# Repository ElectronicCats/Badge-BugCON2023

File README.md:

# Badge BugCON 2023

Badge de la resistencia BugCON 2023 #unetealaresistencia

## Características

- ESP32S3 o RP2040
- UART
- Bluetooth (ESP32S3)
- WiFi (ESP32S3)
- Baterias AA

## License

Diseñado por Electronic Cats para BugCON 2023

Electronic Cats invests time and resources in providing this open-source design. Please support Electronic Cats and open-source hardware by purchasing products from Electronic Cats!

Hardware released under an CERN Open Hardware Licence v1.2. See the LICENSE_HARDWARE file for more information.

Electronic Cats and BugCON is a registered trademark. Please do not use if you sell these PCBs.

Sept 2023

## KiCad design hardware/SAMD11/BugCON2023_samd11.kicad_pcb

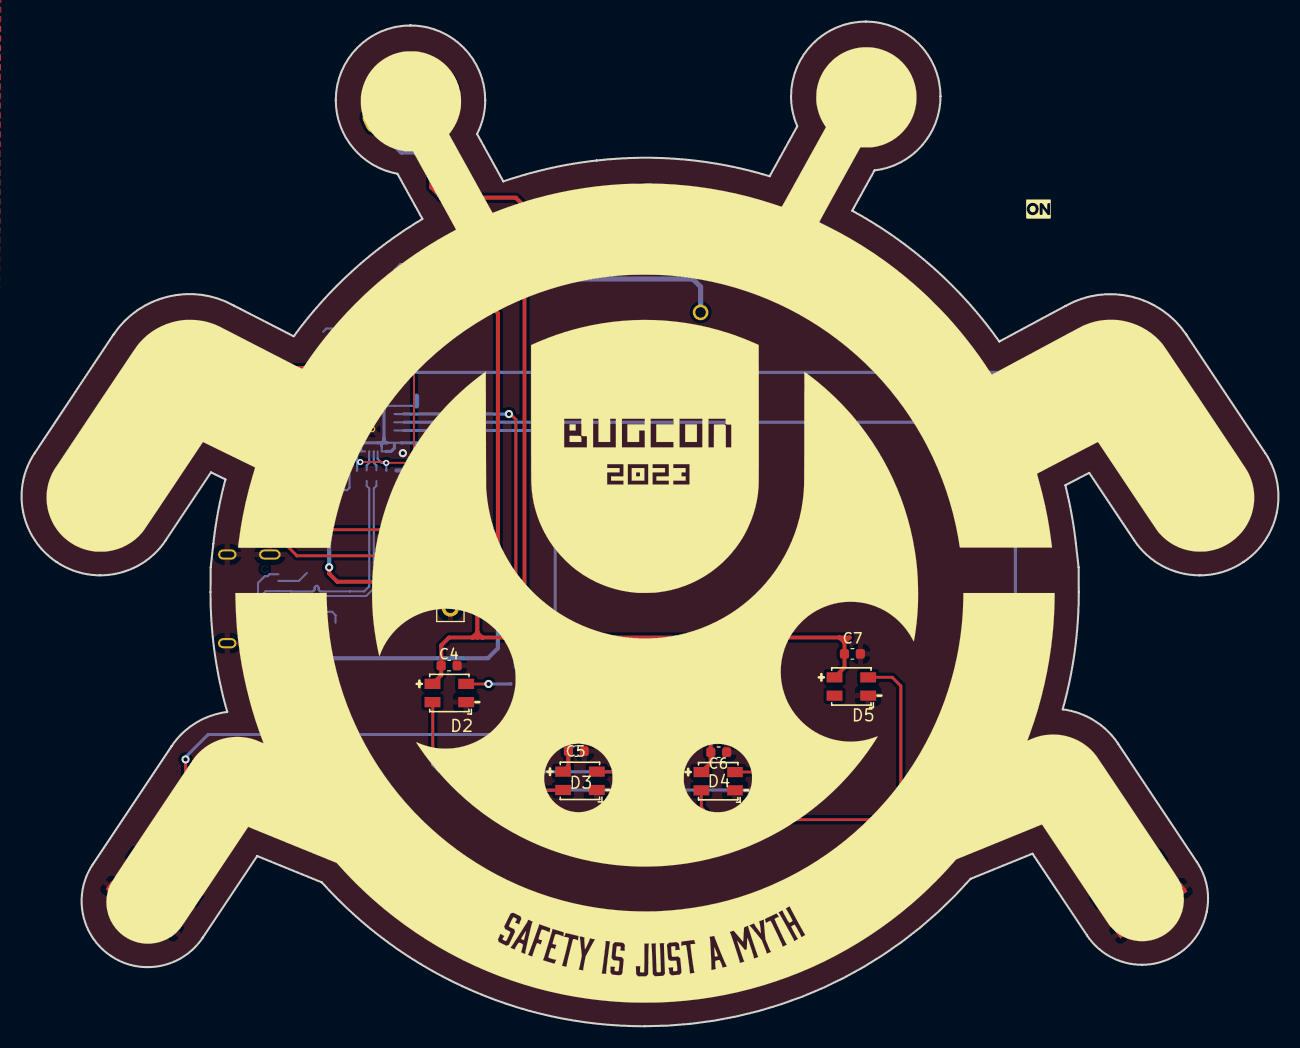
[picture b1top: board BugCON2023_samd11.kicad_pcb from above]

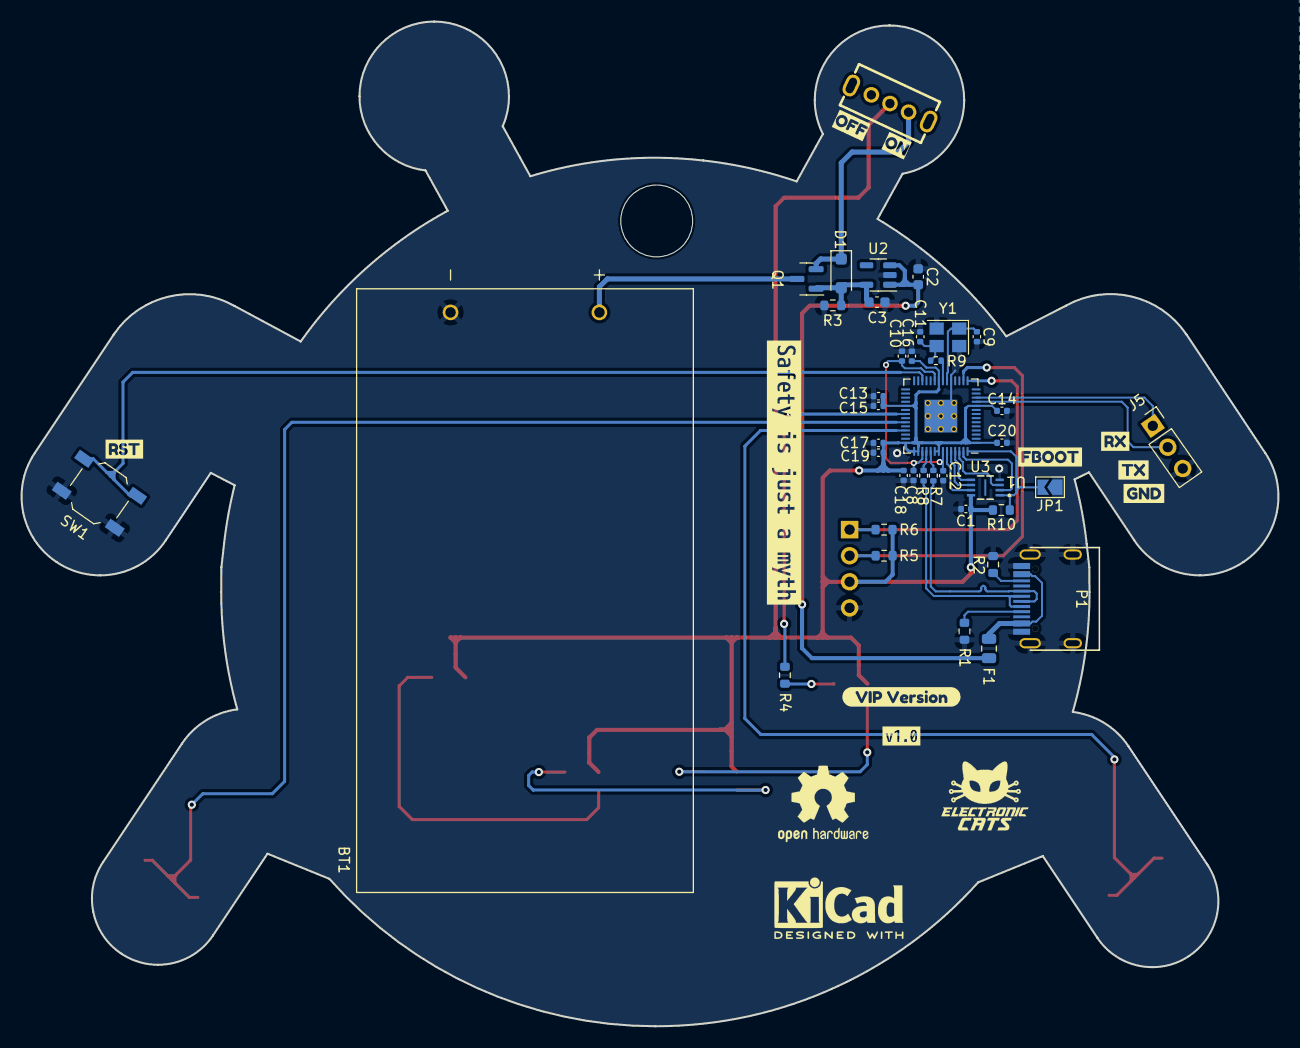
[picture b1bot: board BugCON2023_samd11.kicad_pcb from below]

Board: 2 copper layers, 122.4 x 97.9 mm, 63 parts (49 on the bottom side), 35 nets.

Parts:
BT1: Battery_Cell; BAT_2462
C1, C10, C12, C14, C15, C16, C17, C18, C19, C20: 0.1uF; C_0402_1005Metric
C2, C3: 10uF; C_0603_1608Metric
C4, C5, C6, C7: 0.1uF; C_0603_1608Metric
C8, C13: 1uF; C_0402_1005Metric
C9, C11: 27pF; C_0402_1005Metric
D1: MBR120; D_SOD-123F
D2, D3, D4, D5: WS2812B; LED-SMD_4P-L3.5-W3.5-TL_WS2812B
F1: 0.5A; Fuse_0805_2012Metric
J1: I2C; PinSocket_1x04_P2.54mm_Vertical
J5: Serial; PinSocket_1x03_P2.54mm_Vertical
JP1: BOOT; SolderJumper-2_P1.3mm_Open_TrianglePad1.0x1.5mm
P1: USB_C_Plug_USB2.0; C393939
Q1: DMG3415U-7; SOT-23
R1, R2: 5k1; R_0603_1608Metric
R3: 100K; R_0603_1608Metric
R4: 470; R_0603_1608Metric
R5, R6: 4.7; R_0603_1608Metric
R7, R8: 27; R_0402_1005Metric
R9: 1k; R_0402_1005Metric
R10: 10K; R_0603_1608Metric
Ref**: Val**; Bugcon_svg
SW1: RESET; SW_SPST_TL3342
SW2: ON; SW-TH_SK12D07VG4
SW3, SW4: SW_Push; SW_SPST_TL3342
U1: W25Q16JV; W25Q16JVUXIQ_WIN
U2: AP2112K-3.3; SOT-23-5
U3: RP2040; QFN-56-1EP_7x7mm_P0.4mm_EP3.2x3.2mm
Y1: 12MHz; Crystal_SMD_3225-4Pin_3.2x2.5mm
kibuzzard-652DCDAF: G***; kibuzzard-652DCDAF
kibuzzard-652DCDD3: G***; kibuzzard-652DCDD3
kibuzzard-652DCDF1: G***; kibuzzard-652DCDF1
kibuzzard-652EA30A: G***; kibuzzard-652EA30A
kibuzzard-652EA51A, kibuzzard-652EA51A#2: G***; kibuzzard-652EA51A
kibuzzard-6536E42E: G***; kibuzzard-6536E42E
kibuzzard-6536E385: G***; kibuzzard-6536E385
kibuzzard-6536E415: G***; kibuzzard-6536E415
kibuzzard-6536E422: G***; kibuzzard-6536E422
kibuzzard-6536E471: G***; kibuzzard-6536E471
kibuzzard-6537FB4E: G***; kibuzzard-6537FB4E

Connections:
+1V2: C8.1, C10.1, C12.1, U3.23 (DVDD), U3.45 (VREG_VOUT), U3.50 (DVDD)
+3.3V: C1.1, C4.2, C5.2, C6.2, C7.2, C13.1, C14.1, C15.1, C16.1, C17.1, C18.1, C19.1, C20.1, D2.1 (VDD), D3.1 (VDD), D4.1 (VDD), D5.1 (VDD), J1.3, R5.2, R6.1, R10.1, SW2.2 (B), U1.8 (VCC), U3.1 (IOVDD), U3.10 (IOVDD), U3.22 (IOVDD), U3.33 (IOVDD), U3.42 (IOVDD), U3.43 (ADC_AVDD), U3.44 (VREG_IN), U3.48 (USB_VDD), U3.49 (IOVDD)
+3V3: C3.1, D1.2 (A), Q1.1 (G), R3.1, U2.5 (VOUT)
+BATT: BT1.1 (+), Q1.3 (D)
/D+: P1.A6 (D+), R7.1
/D-: P1.A7 (D-), R8.1
/PB1: SW3.1, U3.39 (GPIO27_ADC1)
/PB2: SW4.1, U3.37 (GPIO25)
/PIN: R4.1, U3.35 (GPIO23)
/QSPI_SCK: U1.6 (CLK), U3.52 (QSPI_SCLK)
/QSPI_SD0: U1.5 (DI(IO0)), U3.53 (QSPI_SD0)
/QSPI_SD1: U1.2 (DO(IO1)), U3.55 (QSPI_SD1)
/QSPI_SD2: U1.3 (IO2), U3.54 (QSPI_SD2)
/QSPI_SD3: U1.7 (IO3), U3.51 (QSPI_SD3)
/QSPI_SS: JP1.2 (B), R10.2, U1.1 (~CS), U3.56 (QSPI_SS)
/RD+: R7.2, U3.47 (USB_DP+)
/RD-: R8.2, U3.46 (USB_DM-)
/RESET: SW1.1, U3.26 (RUN)
/RX: J5.1, U3.12 (GPIO9)
/SCL: J1.2, R5.1, U3.16 (GPIO13)
/SDA: J1.1, R6.2, U3.15 (GPIO12)
/TX: J5.2, U3.11 (GPIO8)
GND: BT1.2 (-), C1.2, C2.2, C3.2, C4.1, C5.1, C6.1, C7.1, C8.2, C9.2, C10.2, C11.2, C12.2, C13.2, C14.2, C15.2, C16.2, C17.2, C18.2, C19.2, C20.2, D2.3 (VSS), D3.3 (VSS), D4.3 (VSS), D5.3 (VSS), J1.4, J5.3, JP1.1 (A), P1.A1 (GND), P1.S1 (SHIELD), R1.1, R2.1, R3.2, SW1.2, SW3.2, SW4.2, U1.4 (GND), U2.2 (GND), U3.19 (TESTEN), U3.57 (GND), Y1.2, Y1.4
unnamed: C11.1, R9.1, Y1.3
unnamed: D1.1 (K), Q1.2 (S), SW2.1 (A)
unnamed: D2.4 (DIN), R4.2
unnamed: D2.2 (DOUT), D3.4 (DIN)
unnamed: D3.2 (DOUT), D4.4 (DIN)
unnamed: D4.2 (DOUT), D5.4 (DIN)
unnamed: F1.1, P1.A4 (VBUS)
unnamed: P1.A5 (CC), R1.2
unnamed: P1.B5 (VCONN), R2.2
unnamed: C9.1, U3.20 (XIN), Y1.1
unnamed: R9.2, U3.21 (XOUT)
VBUS: C2.1, F1.2, U2.1 (VIN), U2.3 (EN)

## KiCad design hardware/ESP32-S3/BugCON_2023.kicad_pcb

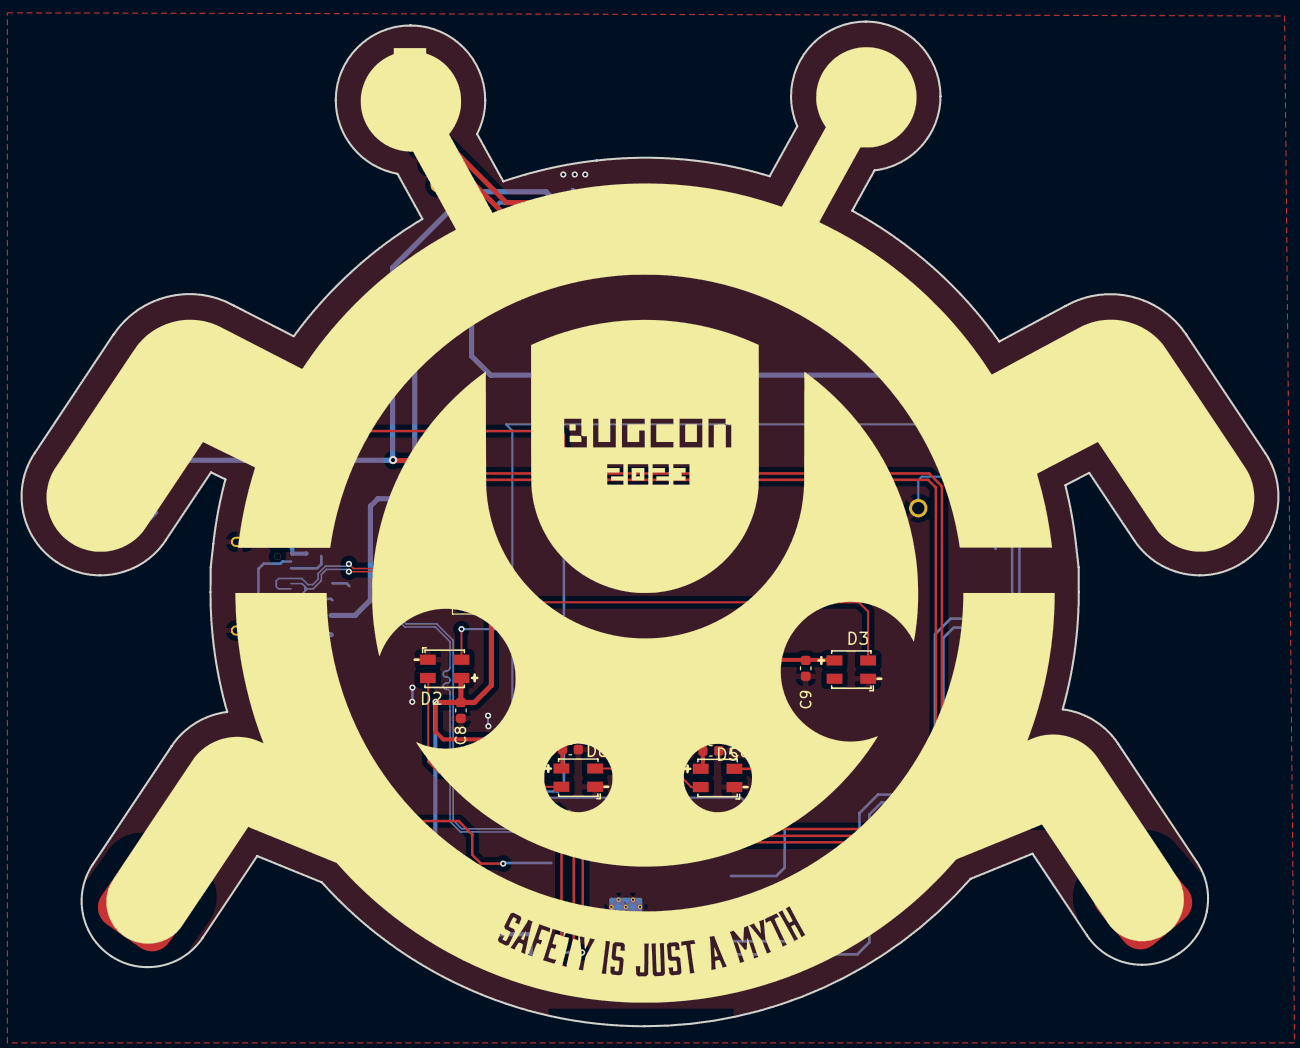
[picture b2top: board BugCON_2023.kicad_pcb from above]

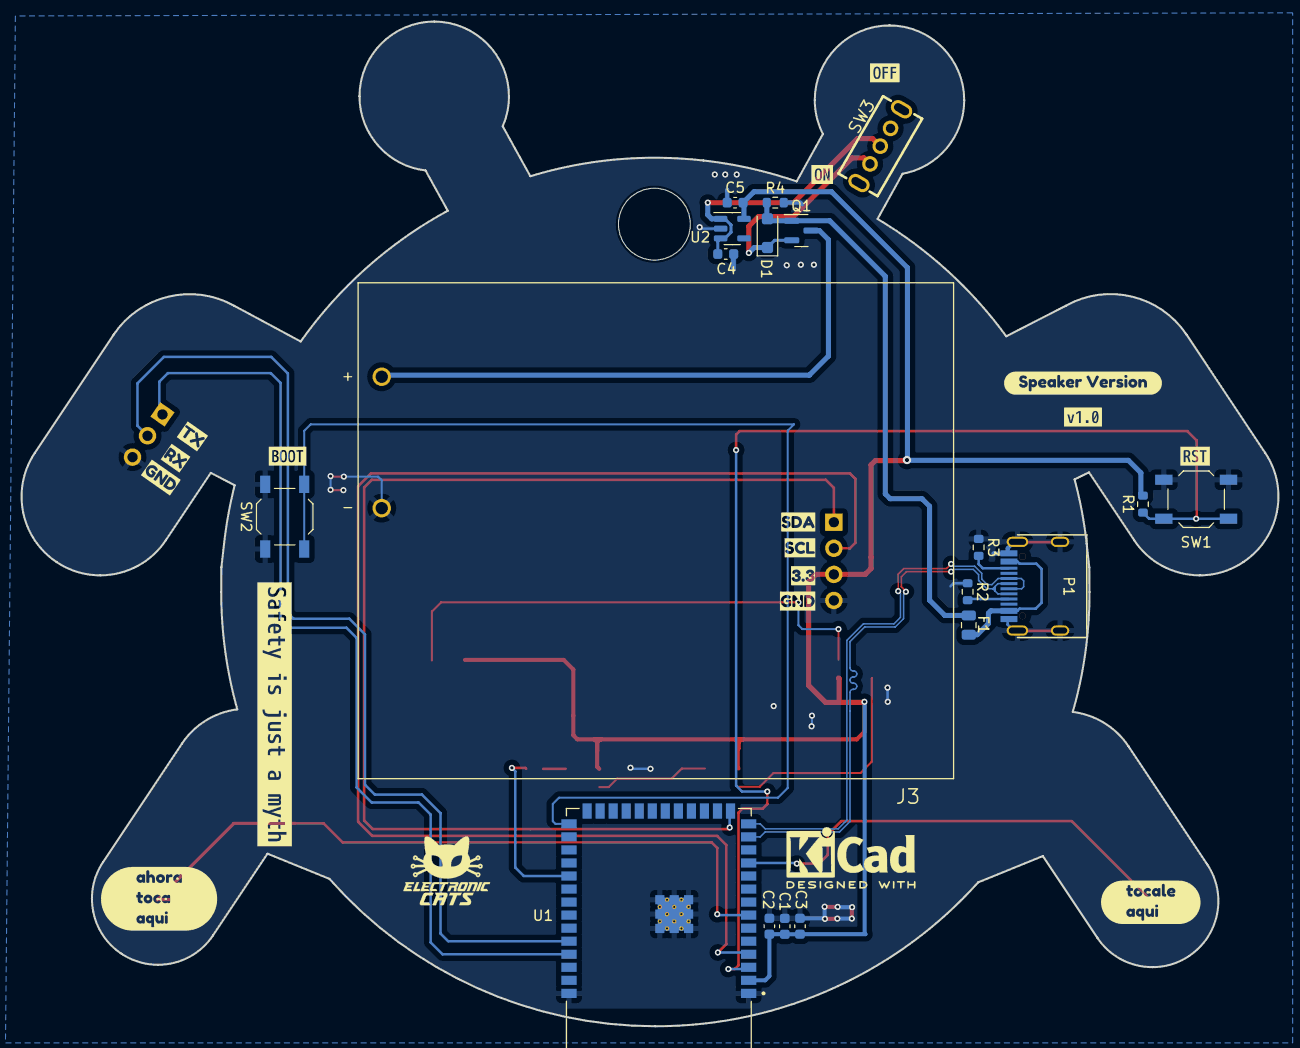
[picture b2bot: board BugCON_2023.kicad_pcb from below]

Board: 2 copper layers, 122.4 x 97.9 mm, 50 parts (35 on the bottom side), 24 nets.

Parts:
C1: 1uF; C_0603_1608Metric
C2, C3, C4, C5: 10uF; C_0603_1608Metric
C6, C7, C8, C9: 0.1uF; C_0603_1608Metric
D1: MBR120; D_SOD-123F
D2, D3, D5, D6: WS2812B; LED-SMD_4P-L3.5-W3.5-TL_WS2812B
F1: 0.5A; Fuse_0805_2012Metric
J1: Conn_01x04_Pin; PinSocket_1x04_P2.54mm_Vertical
J3: Conn_01x02; BAT_12BH331P-GR
J4, J5: Conn_01x01_Pin; PinHeader_1x01_P1.00mm_Horizontal
J6: SERIAL; PinSocket_1x03_P2.54mm_Vertical
P1: USB_C_Plug_USB2.0; C393939
Q1: DMG3415U-7; SOT-23
R1: 10K; R_0603_1608Metric
R2, R3: 5k1; R_0603_1608Metric
R4: 100K; R_0603_1608Metric
R9: 470; R_0603_1608Metric
Ref**: Val**; Bugcon_svg
SW1: RESET; SW_SPST_TL3342
SW2: GPIO; SW_SPST_TL3342
SW3: ON; SW-TH_SK12D07VG4
U1: ESP32-S3-WROOM-1-N4; XCVR_ESP32-S3-WROOM-1-N8R2
U2: AP2112K-3.3; SOT-23-5
kibuzzard-652D8C8F: G***; kibuzzard-652D8C8F
kibuzzard-652D8CA2: G***; kibuzzard-652D8CA2
kibuzzard-652EA3B8: G***; kibuzzard-652EA3B8
kibuzzard-652EA5CF: G***; kibuzzard-652EA5CF
kibuzzard-652EA5F7: G***; kibuzzard-652EA5F7
kibuzzard-652EA30A: G***; kibuzzard-652EA30A
kibuzzard-652EA32D: G***; kibuzzard-652EA32D
kibuzzard-652EA37F: G***; kibuzzard-652EA37F
kibuzzard-652EA51A: G***; kibuzzard-652EA51A
kibuzzard-652EA56E: G***; kibuzzard-652EA56E
kibuzzard-652EA350: G***; kibuzzard-652EA350
kibuzzard-652EA580: G***; kibuzzard-652EA580
kibuzzard-6515D6F9: G***; kibuzzard-6515D6F9
kibuzzard-6515D7CD: G***; kibuzzard-6515D7CD
kibuzzard-6515D70B: G***; kibuzzard-6515D70B
kibuzzard-6515D795, kibuzzard-6515D795#2: G***; kibuzzard-6515D795

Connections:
+3V3: C1.1, C2.1, C3.1, C5.1, C6.2, C7.2, C8.2, C9.2, D2.1 (VDD), D3.1 (VDD), D5.1 (VDD), D6.1 (VDD), J1.3, R1.2, U1.2 (3V3), U2.5 (VOUT)
+BATT: J3.1, Q1.3 (D)
/BOOT: SW2.2, U1.27 (IO0)
/D+: P1.A6 (D+), U1.14 (IO20)
/D-: P1.A7 (D-), U1.13 (IO19)
/PIN: R9.1, U1.31 (IO38)
/RST: R1.1, SW1.2, U1.3 (EN)
/RX: J6.2, U1.36 (RXD0)
/SCL: J1.2, U1.4 (IO4)
/SDA: J1.1, U1.15 (IO3)
/TCH1: J5.1, U1.7 (IO7)
/TCH2: J4.1, U1.11 (IO18)
/TX: J6.1, U1.37 (TXD0)
GND: C1.2, C2.2, C3.2, C4.2, C5.2, C6.1, C7.1, C8.1, C9.1, D2.3 (VSS), D3.3 (VSS), D5.3 (VSS), D6.3 (VSS), J1.4, J3.2, J6.3, P1.A1 (GND), P1.S1 (SHIELD), R2.1, R3.1, R4.2, SW1.1, SW2.1, U1.1 (GND), U1.40 (GND), U2.2 (GND)
unnamed: D1.1 (K), Q1.2 (S), SW3.1 (A)
unnamed: D2.4 (DIN), D6.2 (DOUT)
unnamed: D2.2 (DOUT), D3.4 (DIN)
unnamed: D5.4 (DIN), R9.2
unnamed: D5.2 (DOUT), D6.4 (DIN)
unnamed: F1.1, P1.A4 (VBUS)
unnamed: P1.A5 (CC), R2.2
unnamed: P1.B5 (VCONN), R3.2
unnamed: C4.1, SW3.2 (B), U2.1 (VIN), U2.3 (EN)
VBUS: D1.2 (A), F1.2, Q1.1 (G), R4.1

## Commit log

2023-07-26 Add_PCB
2023-09-22 Add_Schematic
2023-09-22 Add_battery_holder
2023-09-27 add sch of samd11
2023-09-28 First_route_Change_size
2023-09-28 Replace_connector
2023-09-29 Change Place_OLED
2023-09-29 add pcb size, footprints & 3D
2023-09-29 add pins of usb on samd11
2023-10-03 add floorplan to samd11
2023-10-05 Add_Hole
2023-10-05 fix usb traces & add 3d models
2023-10-06 upd floorplan on samd11
2023-10-11 Update_PCB
2023-10-11 upd BOM on Samd11 badge
2023-10-11 upd BOM on esp32 badge
2023-10-11 fix 3.3v label on esp32 badge
2023-10-11 change battery connector
2023-10-13 upd routing and pad connector on samd11
2023-10-16 Replace_serial_conn
2023-10-17 add serial on SAMD11
2023-10-17 Move_ESP32S3
2023-10-17 remove 3.3v on Serial connector on esp32s3
2023-10-17 Change_footprint_USBC
2023-10-17 add logo version speaker
2023-10-17 add more logos
2023-10-17 change MCU for RP2040
2023-10-19 upd floorplan on rp2040 badge
2023-10-19 Change_LED´s_Change_Touch_Pad
2023-10-19 Start new routing RP2040
2023-10-20 Update routing RP2040
2023-10-20 upd BOM and upd silkscreen on RP2040
2023-10-20 Change_Neopixels
2023-10-23 add labels
2023-10-23 change buttons to the front and remove pull up resistors
2023-10-23 Add logos
2023-10-23 Rename_Pullup´s
2023-10-24 add label fboot
2023-11-02 feat: add display test
2023-11-02 feat: add firmware readme
2023-11-04 feat: add esp32s3 support
2023-11-06 test: custom uart pins rp2040
2023-11-06 feat: modify ezbutton library to work with touch sensors
2023-11-07 refactor: buttons definitions
2023-11-07 test: neopixels library
2023-11-08 feat: add previous firmware
2023-11-08 feat: add airtags spoofing example
2023-11-08 feat: add menu class
2023-11-08 refactor: buttons
2023-11-08 refactor: debug class
2023-11-09 feat: add simple menu
2023-11-09 feat: move selected option with buttons
2023-11-09 feat: add chrome dino game
2023-11-09 test: dino game in menu class
2023-11-09 feat: run dino game with buttons
2023-11-09 feat: add export binaries flag
2023-11-09 feat: left button return to main menu in dino game
2023-11-09 feat: add long click
2023-11-10 feat: add long press animation
2023-11-10 docs: add libraries required
2023-11-10 docs: add ssd1306 error fix
2023-11-10 refactor: change menu texts to spanish
2023-11-10 fix: long press animation on esp32
2023-11-10 feat: print hardware info
2023-11-12 fix: esp32 s3 touch sensor not working
2023-11-12 fix: menu buffer overflow
2023-11-13 feat: add leds menu
2023-11-13 test: lower touch threshold
2023-11-13 fix: get touch raw value
2023-11-13 fix: disable old left touch pin
2023-11-13 feat: add airtag emulation
2023-11-14 fix: left touch threshold
2023-11-15 feat: add serial communication
2023-11-15 feat: add pairing banner
2023-11-15 feat: display list of watched talks
2023-11-15 fix: display repeated talks
2023-11-15 feat: add conference help banner
2023-11-15 feat: add pairing success banner
2023-11-16 fix: serial pins esp32s3
2023-11-16 docs(readme): update library list
2023-11-16 fix: broken talk words
2023-11-17 feat: store talks list in flash
2023-11-17 fix: display all talks
2023-11-17 fix: display single line talks
2023-11-17 docs(readme): update production instructions
2023-11-17 feat: add bugcon logo
2023-11-17 fix: conference list memory overflow
2023-11-18 feat: add leds startup animation
2023-11-18 feat: add terminal to main project
2023-11-18 feat: control leds with the terminal
2023-11-18 feat: add terminal menu
2023-11-19 fix: show terminal banner more than once
2023-11-19 feat: add info menu
2023-11-20 feat: add erease flash method
2023-11-21 feat: add web files converter
2023-11-21 feat: add web server files
2023-11-21 fix: leds animation order
2023-11-22 test: index html
2023-11-22 feat: change color of leds from the server
2023-11-22 feat: change neopixel pin
2023-11-22 feat: add pico core support
2023-11-22 feat: add flash storage using pico core
2023-11-22 feat: add arch rp240 macro
2023-11-22 feat: display conference counter
2023-11-22 feat: display wifi params
2023-11-22 feat: active server only on server menu
2023-11-22 feat: disable debug
2023-11-29 add license
2024-05-08 feat:Update LICENSE_HARDWARE.md
